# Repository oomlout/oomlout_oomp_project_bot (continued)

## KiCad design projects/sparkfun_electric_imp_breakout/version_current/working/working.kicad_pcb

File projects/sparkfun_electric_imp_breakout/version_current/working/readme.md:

# OOMP Project  
## Electric_Imp_Breakout  by sparkfun  
  
oomp key: oomp_projects_flat_sparkfun_electric_imp_breakout  
(snippet of original readme)  
  
Electric Imp Breakout  
=====================  
  
[  
*Electric Imp Breakout (BOB-12886)*](https://www.sparkfun.com/products/12886)  
  
The Electric Imp Breakout Board allows you to explore the capabilities of the Imp by providing standard 0.1" headers to solder  
as well as the necessary CryptAuthEE IC to identify your prototype to the Imp Cloud service.   
  
Repository Contents  
-------------------  
* **/Hardware** - All Eagle design files (.brd, .sch)  
* **/Production** - Test bed files and production panel files  
  
Product Versions  
----------------  
* [BOB-11400](https://www.sparkfun.com/products/11400)- Version 1.1 for sale on SparkFun.   
  
Version History  
---------------  
* [v1.1](https://github.com/sparkfun/Electric_Imp_Breakout/tree/V_1.1) Version 1.1 of the Imp Breakout, with the old SD socket footprint.  
  
License Information  
-------------------  
The hardware is released under [Creative Commons ShareAlike 4.0 International](https://creativecommons.org/licenses/by-sa/4.0/).  
  
Distributed as-is; no warranty is given.  
  full source readme at [readme_src.md](readme_src.md)  
  
source repo at: [https://github.com/sparkfun/Electric_Imp_Breakout](https://github.com/sparkfun/Electric_Imp_Breakout)  
## Board  

## Schematic  

[schematic pdf](working_schematic.pdf)  
## Images

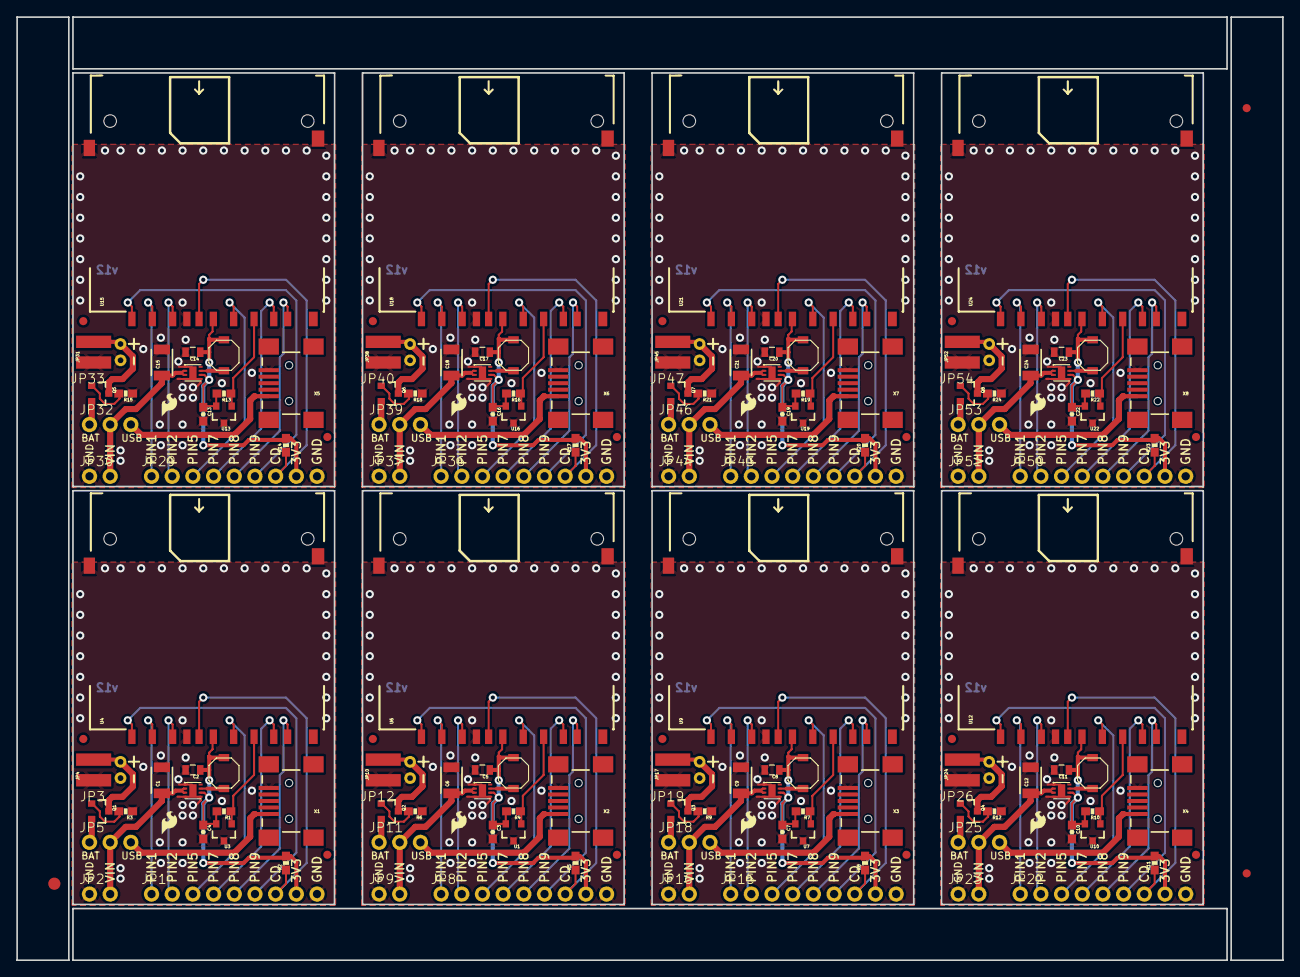
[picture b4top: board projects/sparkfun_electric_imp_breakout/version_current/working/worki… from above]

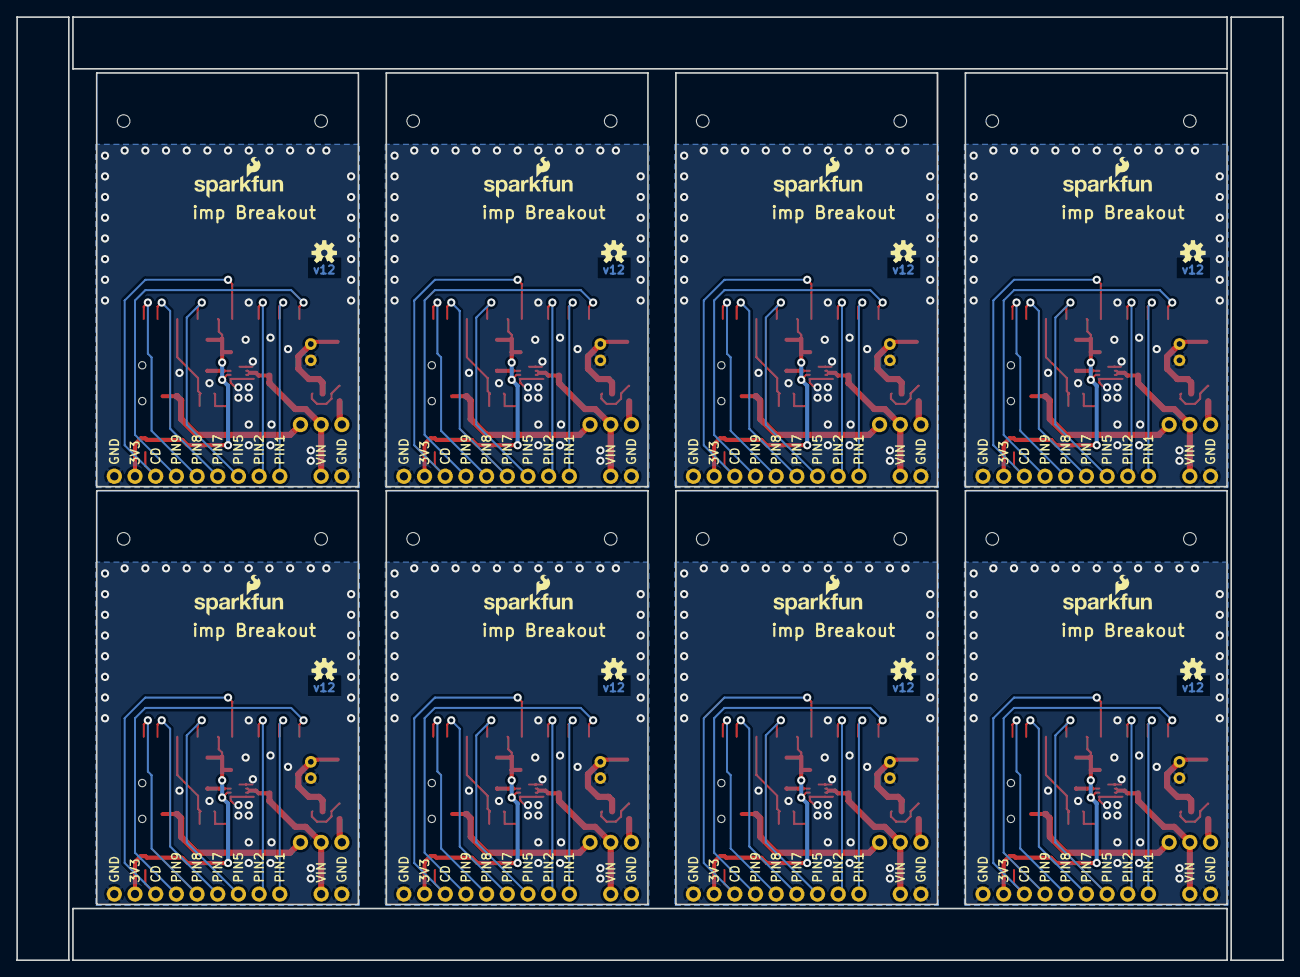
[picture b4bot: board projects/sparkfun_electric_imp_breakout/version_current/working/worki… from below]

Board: 2 copper layers, 155.4 x 115.8 mm, 179 parts (16 on the bottom side), 128 nets.

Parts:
C1, C6, C9, C12, C15, C18, C21, C24: 10uF; 1210
C2, C5, C8, C11, C14, C17, C20, C23: 22uF; 0805
C3, C4, C7, C10, C13, C16, C19, C22: 0.1uF; 0603-CAP
E$1: FIDUCIAL-1.5X3
E$5, E$6: FIDUCIAL-1X2
FID1, FID2, FID3, FID4, FID5, FID6, FID7, FID8, FID9, FID10, FID11, FID12, FID13, FID14, FID15, FID16: FIDUCIAL1X2; FIDUCIAL-1X2
JP1, JP8, JP15, JP22, JP29, JP36, JP43, JP50: M09NO_SILK; 1X09_NO_SILK
JP2, JP9, JP16, JP23, JP30, JP37, JP44, JP51: 1X02_NO_SILK
JP3, JP12, JP19, JP26, JP33, JP40, JP47, JP54: 1X02_SMD
JP4, JP10, JP17, JP24, JP31, JP38, JP45, JP52: JST-2-PTH-NS
JP5, JP11, JP18, JP25, JP32, JP39, JP46, JP53: 1X03_NO_SILK
JP6, JP13, JP20, JP27, JP34, JP41, JP48, JP55: LOGO-SFESK; SFE-LOGO-FLAME
JP7, JP14, JP21, JP28, JP35, JP42, JP49, JP56: SFE_LOGO_NAME_FLAME.1_INCH; SFE_LOGO_NAME_FLAME_.1
L1, L2, L3, L4, L5, L6, L7, L8: 2.2uH; VLF4012A
Q1, Q2, Q3, Q4, Q5, Q6, Q7, Q8: DMG2307L-7; SOT23-3
R1, R3, R4, R6, R7, R9, R10, R12, R13, R15, R16, R18, R19, R21, R22, R24: 100k; 0603-RES
R2, R5, R8, R11, R14, R17, R20, R23: dnp; 0603-RES
U1, U3, U7, U10, U13, U16, U19, U22: ATSHA204-TSU; SOT23-3
U2, U5, U8, U11, U14, U17, U20, U23: TPS62172; WSON-8-PAD
U4, U6, U9, U12, U15, U18, U21, U24: ELECTRIC_IMP; SD_1_1
U$1, U$2, U$3, U$4, U$5, U$6, U$7, U$8: OSHW-LOGOS; OSHW-LOGO-S
X1, X2, X3, X4, X5, X6, X7, X8: USBSMD; USB-MINIB

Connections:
3.3V: C2.1, C4.1, JP1.8, L1.P$2, R1.2, R2.2, U2.6, U3.2, U4.4
3.3V1: C3.1, C5.1, JP8.8, L2.P$2, R4.2, R5.2, U1.2, U5.6, U6.4
3.3V2: C7.1, C8.1, JP15.8, L3.P$2, R7.2, R8.2, U7.2, U8.6, U9.4
3.3V3: C10.1, C11.1, JP22.8, L4.P$2, R10.2, R11.2, U10.2, U11.6, U12.4
3.3V4: C13.1, C14.1, JP29.8, L5.P$2, R13.2, R14.2, U13.2, U14.6, U15.4
3.3V5: C16.1, C17.1, JP36.8, L6.P$2, R16.2, R17.2, U16.2, U17.6, U18.4
3.3V6: C19.1, C20.1, JP43.8, L7.P$2, R19.2, R20.2, U19.2, U20.6, U21.4
3.3V7: C22.1, C23.1, JP50.8, L8.P$2, R22.2, R23.2, U22.2, U23.6, U24.4
CD: JP1.7, R2.1, U4.CD
CD1: JP8.7, R5.1, U6.CD
CD2: JP15.7, R8.1, U9.CD
CD3: JP22.7, R11.1, U12.CD
CD4: JP29.7, R14.1, U15.CD
CD5: JP36.7, R17.1, U18.CD
CD6: JP43.7, R20.1, U21.CD
CD7: JP50.7, R23.1, U24.CD
GND: C1.2, C2.2, C4.2, JP1.9, JP2.1, JP3.1, JP4.1, R3.1, U2.1, U2.4, U2.5, U2.PAD, U3.3, U4.3, U4.SH@1, U4.SH@2, X1.GND
GND1: C3.2, C5.2, C6.2, JP8.9, JP9.1, JP10.1, JP12.1, R6.1, U1.3, U5.1, U5.4, U5.5, U5.PAD, U6.3, U6.SH@1, U6.SH@2, X2.GND
GND2: C7.2, C8.2, C9.2, JP15.9, JP16.1, JP17.1, JP19.1, R9.1, U7.3, U8.1, U8.4, U8.5, U8.PAD, U9.3, U9.SH@1, U9.SH@2, X3.GND
GND3: C10.2, C11.2, C12.2, JP22.9, JP23.1, JP24.1, JP26.1, R12.1, U10.3, U11.1, U11.4, U11.5, U11.PAD, U12.3, U12.SH@1, U12.SH@2, X4.GND
GND4: C13.2, C14.2, C15.2, JP29.9, JP30.1, JP31.1, JP33.1, R15.1, U13.3, U14.1, U14.4, U14.5, U14.PAD, U15.3, U15.SH@1, U15.SH@2, X5.GND
GND5: C16.2, C17.2, C18.2, JP36.9, JP37.1, JP38.1, JP40.1, R18.1, U16.3, U17.1, U17.4, U17.5, U17.PAD, U18.3, U18.SH@1, U18.SH@2, X6.GND
GND6: C19.2, C20.2, C21.2, JP43.9, JP44.1, JP45.1, JP47.1, R21.1, U19.3, U20.1, U20.4, U20.5, U20.PAD, U21.3, U21.SH@1, U21.SH@2, X7.GND
GND7: C22.2, C23.2, C24.2, JP50.9, JP51.1, JP52.1, JP54.1, R24.1, U22.3, U23.1, U23.4, U23.5, U23.PAD, U24.3, U24.SH@1, U24.SH@2, X8.GND
ID: R1.1, U3.1, U4.6
ID1: R4.1, U1.1, U6.6
ID2: R7.1, U7.1, U9.6
ID3: R10.1, U10.1, U12.6
ID4: R13.1, U13.1, U15.6
ID5: R16.1, U16.1, U18.6
ID6: R19.1, U19.1, U21.6
ID7: R22.1, U22.1, U24.6
unnamed: L1.P$1, U2.7
unnamed: Q1.1, R3.2
unnamed: L2.P$1, U5.7
unnamed: JP11.1, Q2.2
unnamed: Q2.1, R6.2
unnamed: JP5.1, Q1.2
unnamed: L3.P$1, U8.7
unnamed: JP18.1, Q3.2
unnamed: Q3.1, R9.2
unnamed: L4.P$1, U11.7
unnamed: JP25.1, Q4.2
unnamed: Q4.1, R12.2
unnamed: L5.P$1, U14.7
unnamed: JP32.1, Q5.2
unnamed: Q5.1, R15.2
unnamed: L6.P$1, U17.7
unnamed: JP39.1, Q6.2
unnamed: Q6.1, R18.2
unnamed: L7.P$1, U20.7
unnamed: JP46.1, Q7.2
unnamed: Q7.1, R21.2
unnamed: L8.P$1, U23.7
unnamed: JP53.1, Q8.2
unnamed: Q8.1, R24.2
PIN1: JP1.1, U4.1
PIN2: JP1.2, U4.2
PIN3: JP8.1, U6.1
PIN4: JP8.2, U6.2
PIN5: JP1.3, U4.5
PIN6: JP8.3, U6.5
PIN7: JP1.4, U4.7
PIN8: JP1.5, U4.8
PIN9: JP1.6, U4.9
PIN10: JP8.4, U6.7
PIN11: JP8.5, U6.8
PIN12: JP8.6, U6.9
PIN13: JP15.1, U9.1
PIN14: JP15.2, U9.2
PIN15: JP15.3, U9.5
PIN16: JP15.4, U9.7
PIN17: JP15.5, U9.8
PIN18: JP15.6, U9.9
PIN19: JP22.1, U12.1
PIN20: JP22.2, U12.2
PIN21: JP22.3, U12.5
PIN22: JP22.4, U12.7
PIN23: JP22.5, U12.8
PIN24: JP22.6, U12.9
PIN25: JP29.1, U15.1
PIN26: JP29.2, U15.2
PIN27: JP29.3, U15.5
PIN28: JP29.4, U15.7
PIN29: JP29.5, U15.8
PIN30: JP29.6, U15.9
PIN31: JP36.1, U18.1
PIN32: JP36.2, U18.2
PIN33: JP36.3, U18.5
PIN34: JP36.4, U18.7
PIN35: JP36.5, U18.8
PIN36: JP36.6, U18.9
PIN37: JP43.1, U21.1
PIN38: JP43.2, U21.2
PIN39: JP43.3, U21.5
PIN40: JP43.4, U21.7
PIN41: JP43.5, U21.8
PIN42: JP43.6, U21.9
PIN43: JP50.1, U24.1
PIN44: JP50.2, U24.2
PIN45: JP50.3, U24.5
PIN46: JP50.4, U24.7
PIN47: JP50.5, U24.8
PIN48: JP50.6, U24.9
VBAT: JP3.2, JP4.2, Q1.3
VBAT1: JP10.2, JP12.2, Q2.3
VBAT2: JP17.2, JP19.2, Q3.3
VBAT3: JP24.2, JP26.2, Q4.3
VBAT4: JP31.2, JP33.2, Q5.3
VBAT5: JP38.2, JP40.2, Q6.3
VBAT6: JP45.2, JP47.2, Q7.3
VBAT7: JP52.2, JP54.2, Q8.3
VIN: C1.1, JP2.2, JP5.2, U2.2, U2.3
VIN1: C6.1, JP9.2, JP11.2, U5.2, U5.3
VIN2: C9.1, JP16.2, JP18.2, U8.2, U8.3
VIN3: C12.1, JP23.2, JP25.2, U11.2, U11.3
VIN4: C15.1, JP30.2, JP32.2, U14.2, U14.3
VIN5: C18.1, JP37.2, JP39.2, U17.2, U17.3
VIN6: C21.1, JP44.2, JP46.2, U20.2, U20.3
VIN7: C24.1, JP51.2, JP53.2, U23.2, U23.3
VUSB: JP5.3, X1.VBUS
VUSB1: JP11.3, X2.VBUS
VUSB2: JP18.3, X3.VBUS
VUSB3: JP25.3, X4.VBUS
VUSB4: JP32.3, X5.VBUS
VUSB5: JP39.3, X6.VBUS
VUSB6: JP46.3, X7.VBUS
VUSB7: JP53.3, X8.VBUS

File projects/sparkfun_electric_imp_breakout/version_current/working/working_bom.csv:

Row,Description,Part,References,Value,Footprint,Quantity Per PCB,Status,Datasheet
1,,0.1UF-25V(+80/-20%)(0603),C4,0.1uF,0603-CAP,1, ,
2,,10UF50V20%(1210),C1,10uF,1210,1, ,
3,,22UF-6.3V-20%(0805),C2,22uF,0805,1, ,
4,,FRAME-LETTER,FRAME1,FRAME-LETTER,CREATIVE_COMMONS,1, ,
5,,LOGO-SFESK,JP6,LOGO-SFESK,SFE-LOGO-FLAME,1, ,
6,,M02-JST-2-PTH-NO_SILK,JP4,M02-JST-2-PTH-NO_SILK,JST-2-PTH-NS,1, ,
7,,M021X02_NO_SILK,JP2,M021X02_NO_SILK,1X02_NO_SILK,1, ,
8,,M02SMD,JP3,M02SMD,1X02_SMD,1, ,
9,,M031X03_NO_SILK,JP5,M031X03_NO_SILK,1X03_NO_SILK,1, ,
10,,M09NO_SILK,JP1,M09NO_SILK,1X09_NO_SILK,1, ,
11,,SFE_LOGO_NAME_FLAME.1_INCH,JP7,SFE_LOGO_NAME_FLAME.1_INCH,SFE_LOGO_NAME_FLAME_.1,1, ,
12,,INDUCTORVLF4012A,L1,2.2uH,VLF4012A,1, ,
13,,MOSFET-PCHANNELSMD,Q1,MOSFET-PCHANNELSMD,SOT23-3,1, ,
14,,100KOHM1/10W1%(0603),R1 R3,100k,0603-RES,2, ,
15,,ATSHA204-TSU,U3,ATSHA204-TSU,SOT23-3,1, ,
16,,ELECTRIC_IMP,U4,ELECTRIC_IMP,SD_1_1,1, ,
17,,TPS62172,U2,TPS62172,WSON-8-PAD,1, ,
18,,OSHW-LOGOS,U$5,OSHW-LOGOS,OSHW-LOGO-S,1, ,
19,,REVISION,U$3,REVISION,REVISION,1, ,
20,,USBSMD,X1,USBSMD,USB-MINIB,1, ,





Project info:
Schematic:,working
Variant:,default
Revision:,
Date:,2023-08-06_12-56-01
KiCad Version:,7.0.6-7.0.6~ubuntu22.04.1
Statistics:
Component Groups:,21
Component Count:,22 (0 SMD/ 0 THT)
Fitted Components:,21 (0 SMD/ 0 THT)
Number of PCBs:,1
Total Components:,21

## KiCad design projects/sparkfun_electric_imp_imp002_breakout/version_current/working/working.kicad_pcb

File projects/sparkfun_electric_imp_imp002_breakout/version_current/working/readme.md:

# OOMP Project  
## Electric_Imp_imp002_Breakout  by sparkfun  
  
oomp key: oomp_projects_flat_sparkfun_electric_imp_imp002_breakout  
(snippet of original readme)  
  
SparkFun Electric Imp imp002 Breakout  
============================  

[*Electric Imp imp002 Breakout (BOB-12958)*](https://www.sparkfun.com/products/12958)  
  
The imp002 is a surface mount Electric Imp module with its own breakout board and more pins than the original imp001 card.  

Repository Contents  
-------------------  
* **/Documentation** - SVG files of the board layout.  
* **/Hardware** - Eagle PCB layout files  
* **/Production** - Files to support SparkFun production  
  
Documentation  
--------------  
  
* **[Hookup Guide](https://learn.sparkfun.com/tutorials/electric-imp-breakout-hookup-guide)** - Basic hookup guide  
  
Product Versions  
----------------  
  
* [BOB-12958](https://www.sparkfun.com/products/12958)- Hardware version 1.0.   
  
Version History  
---------------  
  
License Information  
-------------------  
  
This product is _**open source**_!   
  
Please review the LICENSE.md file for license information.   
  
If you have any questions or concerns on licensing, please contact techsupport@sparkfun.com.  
  
Distributed as-is; no warranty is given.  
  
- Your friends at SparkFun.  
  
  full source readme at [readme_src.md](readme_src.md)  
  
source repo at: [https://github.com/sparkfun/Electric_Imp_imp002_Breakout](https://github.com/sparkfun/Electric_Imp_imp002_Breakout)  
## Board  

## Schematic  

[schematic pdf](working_schematic.pdf)  
## Images

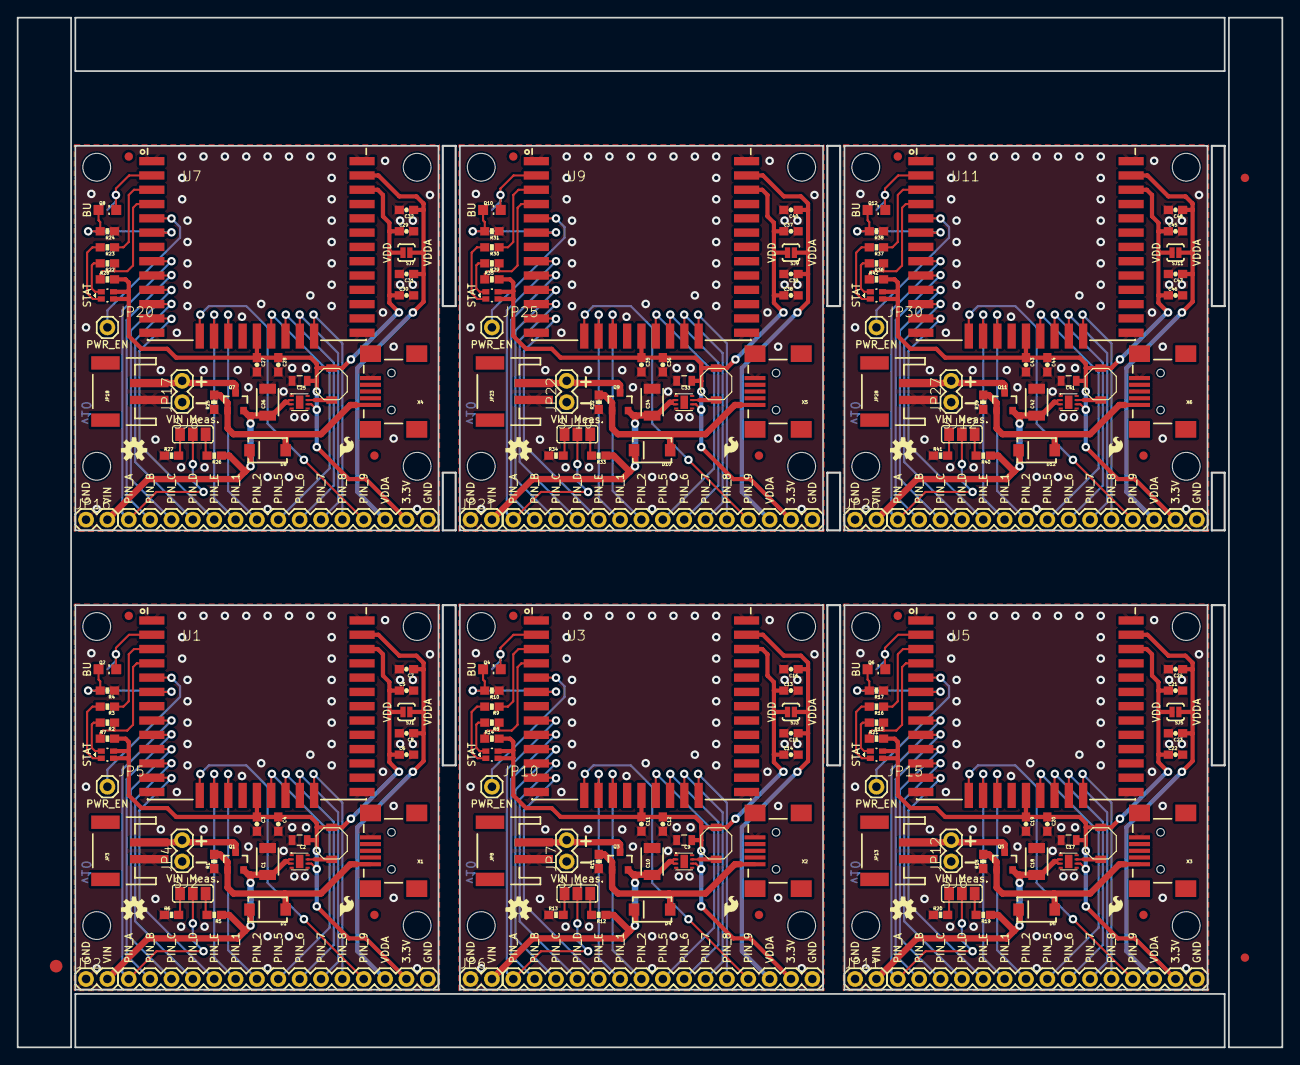
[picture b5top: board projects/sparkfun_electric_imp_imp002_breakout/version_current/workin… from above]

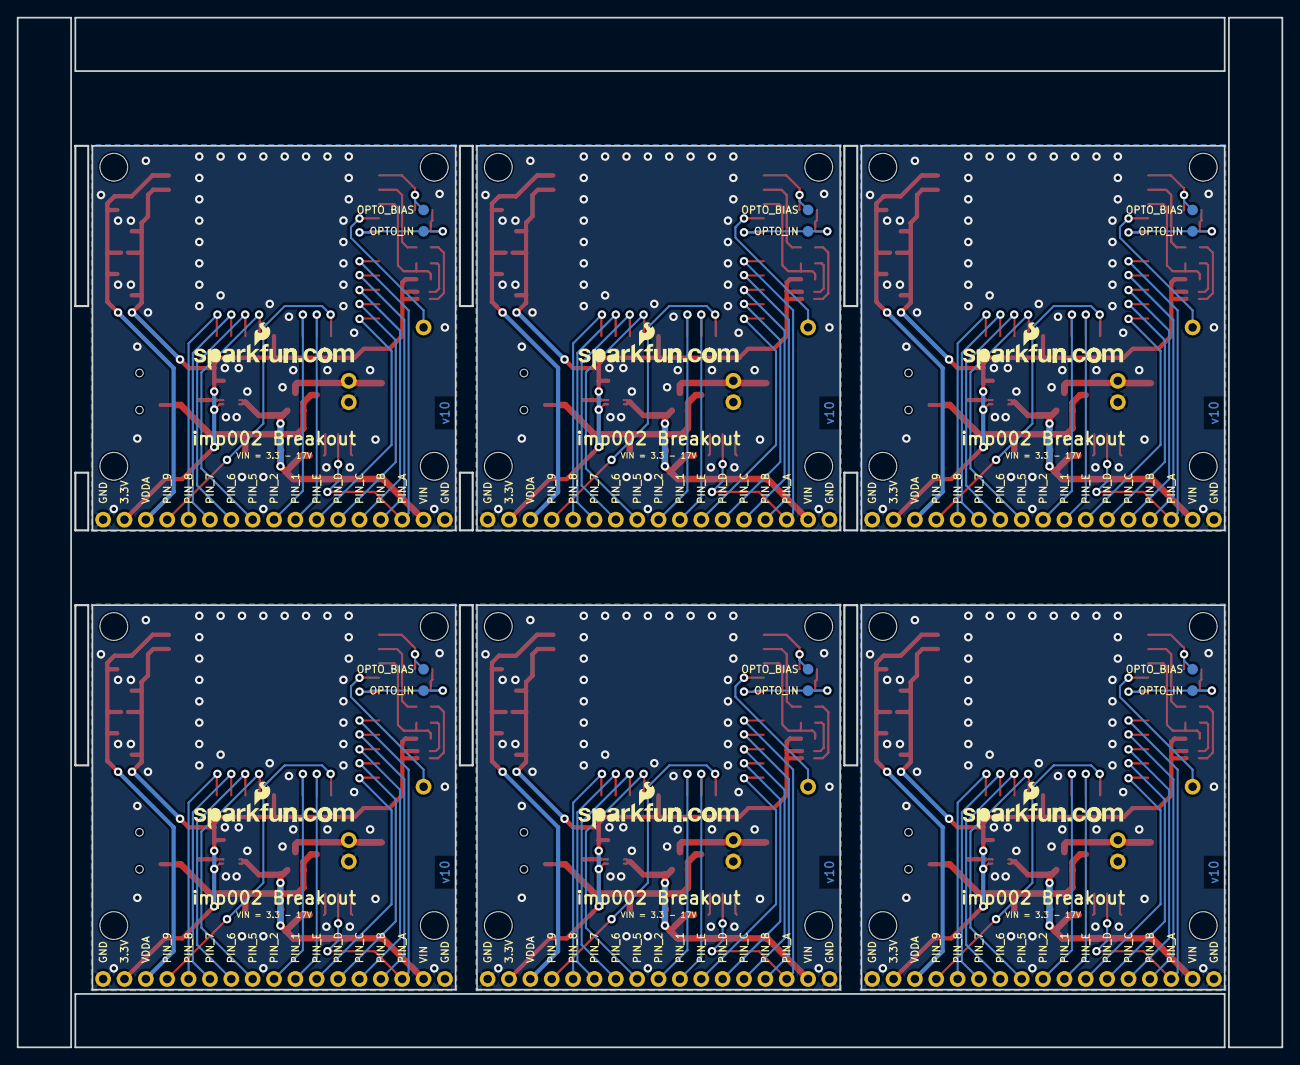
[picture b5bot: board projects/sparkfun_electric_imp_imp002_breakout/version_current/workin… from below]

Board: 4 copper layers, 150.4 x 122.4 mm, 249 parts (18 on the bottom side), 168 nets.

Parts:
C1, C10, C18, C26, C34, C42: 10uF; 1210
C2, C9, C17, C25, C33, C41: 22uF; 0805
C3, C5, C7, C11, C13, C16, C19, C21, C24, C27, C29, C32, C35, C37, C40, C43, C45, C48: 100pF; 0603-CAP
C4, C6, C12, C14, C20, C22, C28, C30, C36, C38, C44, C46: 1.0uF; 0603-CAP
C8, C15, C23, C31, C39, C47: DNP; 0603-CAP
D1, D4, D6, D8, D10, D12: MBRA140; SMA-DIODE
D2, D3, D5, D7, D9, D11: LED-RGLTST-C195KGJRKT; LTST-C195KGJRKT
E$1: FIDUCIAL-1.5X3
E$3, E$5: FIDUCIAL-1X2
FID1, FID2, FID3, FID4, FID5, FID6, FID7, FID8, FID9, FID10, FID11, FID12: FIDUCIAL1X2; FIDUCIAL-1X2
JP1, JP9, JP14, JP19, JP24, JP29: M15; 1X15
JP2, JP4, JP6, JP7, JP11, JP12, JP16, JP17, JP21, JP22, JP26, JP27: M02PTH; 1X02
JP3, JP8, JP13, JP18, JP23, JP28: M02-JST-2MM-SMT; JST-2-SMD
JP5, JP10, JP15, JP20, JP25, JP30: M01PTH; 1X01
L1, L2, L3, L4, L5, L6: 2.2uH; VLF4012A
LOGO1, LOGO3, LOGO5, LOGO7, LOGO9, LOGO11: OSHW-LOGOS; OSHW-LOGO-S
LOGO2, LOGO4, LOGO6, LOGO8, LOGO10, LOGO12: SFE_LOGO_FLAME.1_INCH; SFE_LOGO_FLAME_.1
Q1, Q3, Q5, Q7, Q9, Q11: DMG2307L; SOT23-3
Q2, Q4, Q6, Q8, Q10, Q12: PT17-21C-L41-TR8
R1, R11, R18, R25, R32, R39: 100k; 0603-RES
R2, R3, R8, R9, R15, R16, R22, R23, R29, R30, R36, R37: 330; 0603-RES
R4, R5, R10, R12, R17, R19, R24, R26, R31, R33, R38, R40: 33k; 0603-RES
R6, R13, R20, R27, R34, R41: 62k; 0603-RES
R7, R14, R21, R28, R35, R42: 10K; 0603-RES
SJ1, SJ3, SJ5, SJ7, SJ9, SJ11: JUMPER-PAD-2-NC_BY_PASTE; PAD-JUMPER-2-NC_BY_PASTE_YES_SILK
SJ2, SJ4, SJ6, SJ8, SJ10, SJ12: JUMPER-PAD-3-NOFULL_BOX_SILK; PAD-JUMPER-3-NO_YES_SILK_FULL_BOX
STANDOFF1, STANDOFF2, STANDOFF3, STANDOFF4, STANDOFF5, STANDOFF6, STANDOFF7, STANDOFF8, STANDOFF9, STANDOFF10, STANDOFF11, STANDOFF12, STANDOFF13, STANDOFF14, STANDOFF15, STANDOFF16, STANDOFF17, STANDOFF18, STANDOFF19, STANDOFF20, STANDOFF21, STANDOFF22, STANDOFF23, STANDOFF24: STAND-OFF
TP1, TP2, TP3, TP4, TP5, TP6, TP7, TP8, TP9, TP10, TP11, TP12: TEST-POINT3X5; PAD.03X.05
U1, U3, U5, U7, U9, U11: imp002; ELECTRIC_IMP_IMP002
U2, U4, U6, U8, U10, U12: TPS62172; WSON-8-PAD
U$1, U$2, U$3, U$4, U$5, U$9: SFE_LOGO_NAME_WEB; SFE-NEW-WEBLOGO
X1, X2, X3, X4, X5, X6: USBSMD; USB-MINIB

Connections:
3.3V: C2.1, C3.1, C4.1, C5.1, C6.1, D2.P$1, D2.P$2, JP1.2, L1.P$2, R7.2, SJ1.2, U1.18, U1.33, U2.6
3.3V1: C9.1, C11.1, C12.1, C13.1, C14.1, D3.P$1, D3.P$2, JP9.2, L2.P$2, R14.2, SJ3.2, U3.18, U3.33, U4.6
3.3V2: C17.1, C19.1, C20.1, C21.1, C22.1, D5.P$1, D5.P$2, JP14.2, L3.P$2, R21.2, SJ5.2, U5.18, U5.33, U6.6
3.3V3: C25.1, C27.1, C28.1, C29.1, C30.1, D7.P$1, D7.P$2, JP19.2, L4.P$2, R28.2, SJ7.2, U7.18, U7.33, U8.6
3.3V4: C33.1, C35.1, C36.1, C37.1, C38.1, D9.P$1, D9.P$2, JP24.2, L5.P$2, R35.2, SJ9.2, U9.18, U9.33, U10.6
3.3V5: C41.1, C43.1, C44.1, C45.1, C46.1, D11.P$1, D11.P$2, JP29.2, L6.P$2, R42.2, SJ11.2, U11.18, U11.33, U12.6
GND: C1.2, C2.2, C3.2, C4.2, C5.2, C6.2, C7.2, C8.2, JP1.1, JP2.1, JP3.1, JP4.1, R1.1, R4.1, R6.1, U1.1, U1.7, U1.13, U1.17, U1.23, U1.24, U1.25, U1.26, U1.27, U1.28, U1.29, U1.30, U1.31, U1.32, U1.35, U2.1, U2.4, U2.5, U2.PAD, X1.GND
GND1: C9.2, C10.2, C11.2, C12.2, C13.2, C14.2, C15.2, C16.2, JP6.1, JP7.1, JP8.1, JP9.1, R10.1, R11.1, R13.1, U3.1, U3.7, U3.13, U3.17, U3.23, U3.24, U3.25, U3.26, U3.27, U3.28, U3.29, U3.30, U3.31, U3.32, U3.35, U4.1, U4.4, U4.5, U4.PAD, X2.GND
GND2: C17.2, C18.2, C19.2, C20.2, C21.2, C22.2, C23.2, C24.2, JP11.1, JP12.1, JP13.1, JP14.1, R17.1, R18.1, R20.1, U5.1, U5.7, U5.13, U5.17, U5.23, U5.24, U5.25, U5.26, U5.27, U5.28, U5.29, U5.30, U5.31, U5.32, U5.35, U6.1, U6.4, U6.5, U6.PAD, X3.GND
GND3: C25.2, C26.2, C27.2, C28.2, C29.2, C30.2, C31.2, C32.2, JP16.1, JP17.1, JP18.1, JP19.1, R24.1, R25.1, R27.1, U7.1, U7.7, U7.13, U7.17, U7.23, U7.24, U7.25, U7.26, U7.27, U7.28, U7.29, U7.30, U7.31, U7.32, U7.35, U8.1, U8.4, U8.5, U8.PAD, X4.GND
GND4: C33.2, C34.2, C35.2, C36.2, C37.2, C38.2, C39.2, C40.2, JP21.1, JP22.1, JP23.1, JP24.1, R31.1, R32.1, R34.1, U9.1, U9.7, U9.13, U9.17, U9.23, U9.24, U9.25, U9.26, U9.27, U9.28, U9.29, U9.30, U9.31, U9.32, U9.35, U10.1, U10.4, U10.5, U10.PAD, X5.GND
GND5: C41.2, C42.2, C43.2, C44.2, C45.2, C46.2, C47.2, C48.2, JP26.1, JP27.1, JP28.1, JP29.1, R38.1, R39.1, R41.1, U11.1, U11.7, U11.13, U11.17, U11.23, U11.24, U11.25, U11.26, U11.27, U11.28, U11.29, U11.30, U11.31, U11.32, U11.35, U12.1, U12.4, U12.5, U12.PAD, X6.GND
LED_G: R3.1, U1.3
LED_G1: R9.1, U3.3
LED_G2: R16.1, U5.3
LED_G3: R23.1, U7.3
LED_G4: R30.1, U9.3
LED_G5: R37.1, U11.3
LED_R: R2.1, R7.1, U1.4
LED_R1: R8.1, R14.1, U3.4
LED_R2: R15.1, R21.1, U5.4
LED_R3: R22.1, R28.1, U7.4
LED_R4: R29.1, R35.1, U9.4
LED_R5: R36.1, R42.1, U11.4
unnamed: L1.P$1, U2.7
unnamed: D1.A, Q1.1, R1.2, X1.VBUS
unnamed: L2.P$1, U4.7
unnamed: D2.P$4, R2.2
unnamed: D2.P$3, R3.2
unnamed: R5.2, SJ2.3
unnamed: R6.2, SJ2.1
unnamed: D3.P$4, R8.2
unnamed: D3.P$3, R9.2
unnamed: D4.A, Q3.1, R11.2, X2.VBUS
unnamed: R12.2, SJ4.3
unnamed: R13.2, SJ4.1
unnamed: L3.P$1, U6.7
unnamed: D5.P$4, R15.2
unnamed: D5.P$3, R16.2
unnamed: D6.A, Q5.1, R18.2, X3.VBUS
unnamed: R19.2, SJ6.3
unnamed: R20.2, SJ6.1
unnamed: L4.P$1, U8.7
unnamed: D7.P$4, R22.2
unnamed: D7.P$3, R23.2
unnamed: D8.A, Q7.1, R25.2, X4.VBUS
unnamed: R26.2, SJ8.3
unnamed: R27.2, SJ8.1
unnamed: L5.P$1, U10.7
unnamed: D9.P$4, R29.2
unnamed: D9.P$3, R30.2
unnamed: D10.A, Q9.1, R32.2, X5.VBUS
unnamed: R33.2, SJ10.3
unnamed: R34.2, SJ10.1
unnamed: L6.P$1, U12.7
unnamed: D11.P$4, R36.2
unnamed: D11.P$3, R37.2
unnamed: D12.A, Q11.1, R39.2, X6.VBUS
unnamed: R40.2, SJ12.3
unnamed: R41.2, SJ12.1
OPTO_BIAS: Q2.C, TP1.P$1, U1.2
OPTO_BIAS1: Q4.C, TP3.P$1, U3.2
OPTO_BIAS2: Q6.C, TP5.P$1, U5.2
OPTO_BIAS3: Q8.C, TP7.P$1, U7.2
OPTO_BIAS4: Q10.C, TP9.P$1, U9.2
OPTO_BIAS5: Q12.C, TP11.P$1, U11.2
OPTO_IN: Q2.E, R4.2, TP2.P$1, U1.6
OPTO_IN1: Q4.E, R10.2, TP4.P$1, U3.6
OPTO_IN2: Q6.E, R17.2, TP6.P$1, U5.6
OPTO_IN3: Q8.E, R24.2, TP8.P$1, U7.6
OPTO_IN4: Q10.E, R31.2, TP10.P$1, U9.6
OPTO_IN5: Q12.E, R38.2, TP12.P$1, U11.6
PIN_1: JP1.10, U1.15
PIN_2: JP1.9, U1.16
PIN_3: JP9.10, U3.15
PIN_4: JP9.9, U3.16
PIN_5: JP1.8, U1.19
PIN_6: JP1.7, U1.20
PIN_7: JP1.6, U1.21
PIN_8: JP1.5, U1.22
PIN_9: JP1.4, U1.14
PIN_10: JP9.8, U3.19
PIN_11: JP9.7, U3.20
PIN_12: JP9.6, U3.21
PIN_13: JP9.5, U3.22
PIN_14: JP9.4, U3.14
PIN_15: JP14.10, U5.15
PIN_16: JP14.9, U5.16
PIN_17: JP14.8, U5.19
PIN_18: JP14.7, U5.20
PIN_19: JP14.6, U5.21
PIN_20: JP14.5, U5.22
PIN_21: JP14.4, U5.14
PIN_22: JP19.10, U7.15
PIN_23: JP19.9, U7.16
PIN_24: JP19.8, U7.19
PIN_25: JP19.7, U7.20
PIN_26: JP19.6, U7.21
PIN_27: JP19.5, U7.22
PIN_28: JP19.4, U7.14
PIN_29: JP24.10, U9.15
PIN_30: JP24.9, U9.16
PIN_31: JP24.8, U9.19
PIN_32: JP24.7, U9.20
PIN_33: JP24.6, U9.21
PIN_34: JP24.5, U9.22
PIN_35: JP24.4, U9.14
PIN_36: JP29.10, U11.15
PIN_37: JP29.9, U11.16
PIN_38: JP29.8, U11.19
PIN_39: JP29.7, U11.20
PIN_40: JP29.6, U11.21
PIN_41: JP29.5, U11.22
PIN_42: JP29.4, U11.14
PIN_A: JP1.15, SJ2.2, U1.8
PIN_A1: JP9.15, SJ4.2, U3.8
PIN_A2: JP14.15, SJ6.2, U5.8
PIN_A3: JP19.15, SJ8.2, U7.8
PIN_A4: JP24.15, SJ10.2, U9.8
PIN_A5: JP29.15, SJ12.2, U11.8
PIN_B: JP1.14, U1.9
PIN_B1: JP9.14, U3.9
PIN_B2: JP14.14, U5.9
PIN_B3: JP19.14, U7.9
PIN_B4: JP24.14, U9.9
PIN_B5: JP29.14, U11.9
PIN_C: JP1.13, U1.10
PIN_C1: JP9.13, U3.10
PIN_C2: JP14.13, U5.10
PIN_C3: JP19.13, U7.10
PIN_C4: JP24.13, U9.10
PIN_C5: JP29.13, U11.10
PIN_D: JP1.12, U1.11
PIN_D1: JP9.12, U3.11
PIN_D2: JP14.12, U5.11
PIN_D3: JP19.12, U7.11
PIN_D4: JP24.12, U9.11
PIN_D5: JP29.12, U11.11
PIN_E: JP1.11, U1.12
PIN_E1: JP9.11, U3.12
PIN_E2: JP14.11, U5.12
PIN_E3: JP19.11, U7.12
PIN_E4: JP24.11, U9.12
PIN_E5: JP29.11, U11.12
POWER_EN: JP5.1, U1.5
POWER_EN1: JP10.1, U3.5
POWER_EN2: JP15.1, U5.5
POWER_EN3: JP20.1, U7.5
POWER_EN4: JP25.1, U9.5
POWER_EN5: JP30.1, U11.5
VBAT: JP3.2, JP4.2, Q1.3
VBAT1: JP7.2, JP8.2, Q3.3
VBAT2: JP12.2, JP13.2, Q5.3
VBAT3: JP17.2, JP18.2, Q7.3
VBAT4: JP22.2, JP23.2, Q9.3
VBAT5: JP27.2, JP28.2, Q11.3
VDDA: C7.1, C8.1, JP1.3, SJ1.1, U1.34
VDDA1: C15.1, C16.1, JP9.3, SJ3.1, U3.34
VDDA2: C23.1, C24.1, JP14.3, SJ5.1, U5.34
VDDA3: C31.1, C32.1, JP19.3, SJ7.1, U7.34
VDDA4: C39.1, C40.1, JP24.3, SJ9.1, U9.34
VDDA5: C47.1, C48.1, JP29.3, SJ11.1, U11.34
VIN: C1.1, D1.C, JP2.2, Q1.2, R5.1, U2.2, U2.3
VIN1: C10.1, D4.C, JP6.2, Q3.2, R12.1, U4.2, U4.3
VIN2: C18.1, D6.C, JP11.2, Q5.2, R19.1, U6.2, U6.3
VIN3: C26.1, D8.C, JP16.2, Q7.2, R26.1, U8.2, U8.3
VIN4: C34.1, D10.C, JP21.2, Q9.2, R33.1, U10.2, U10.3
VIN5: C42.1, D12.C, JP26.2, Q11.2, R40.1, U12.2, U12.3

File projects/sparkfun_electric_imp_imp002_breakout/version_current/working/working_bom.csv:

Row,Description,Part,References,Value,Footprint,Quantity Per PCB,Status,Datasheet,PROD_ID
1,,SparkFun-Capacitors_CAP0603-CAP,C3 C5 C7,100pF,0603-CAP,3, ,,CAP-07883
2,,1.0UF-16V-10%(0603),C4 C6,1.0uF,0603-CAP,2, ,,
3,,CAP1210,C1,10uF,1210,1, ,,
4,,CAP0805,C2,22uF,0805,1, ,,CAP-08402
5,,DIODE-SCHOTTKY-MBRA140,D1,DIODE-SCHOTTKY-MBRA140,SMA-DIODE,1, ,,
6,,LED-RGLTST-C195KGJRKT,D2,LED-RGLTST-C195KGJRKT,LTST-C195KGJRKT,1, ,,
7,,FRAME-LETTER,FRAME1,FRAME-LETTER,CREATIVE_COMMONS,1, ,,
8,,M01PTH,JP5,M01PTH,1X01,1, ,,
9,,M02-JST-2MM-SMT,JP3,M02-JST-2MM-SMT,JST-2-SMD,1, ,,
10,,M02PTH,JP2 JP4,M02PTH,1X02,2, ,,
11,,M15,JP1,M15,1X15,1, ,,
12,,INDUCTORVLF4012A,L1,2.2uH,VLF4012A,1, ,,
13,,OSHW-LOGOS,LOGO1,OSHW-LOGOS,OSHW-LOGO-S,1, ,,
14,,SFE_LOGO_FLAME.1_INCH,LOGO2,SFE_LOGO_FLAME.1_INCH,SFE_LOGO_FLAME_.1,1, ,,
15,,MOSFET-PCHANNELDMG2307L,Q1,MOSFET-PCHANNELDMG2307L,SOT23-3,1, ,,
16,,PHOTOTRANSISTORPT17-21C-L41-TR8,Q2,PT17-21C-L41-TR8,PT17-21C-L41-TR8,1, ,,
17,,330OHM1/10W1%(0603),R2 R3,330,0603-RES,2, ,,
18,,10KOHM1/10W1%(0603)0603,R7,10K,0603-RES,1, ,,
19,,33KOHM1/10W1%(0603),R4 R5,33k,0603-RES,2, ,,
20,,RESISTOR0603,R6,62k,0603-RES,1, ,,RES-09993
21,,100KOHM1/10W1%(0603),R1,100k,0603-RES,1, ,,
22,,JUMPER-PAD-2-NC_BY_PASTE,SJ1,JUMPER-PAD-2-NC_BY_PASTE,PAD-JUMPER-2-NC_BY_PASTE_YES_SILK,1, ,,
23,,JUMPER-PAD-3-NOFULL_BOX_SILK,SJ2,JUMPER-PAD-3-NOFULL_BOX_SILK,PAD-JUMPER-3-NO_YES_SILK_FULL_BOX,1, ,,
24,,STAND-OFF,STANDOFF1 STANDOFF2 STANDOFF3 STANDOFF4,STAND-OFF,STAND-OFF,4, ,,
25,,ELECTRIC_IMP_IMP002,U1,ELECTRIC_IMP_IMP002,ELECTRIC_IMP_IMP002,1, ,,
26,,TPS62172,U2,TPS62172,WSON-8-PAD,1, ,,
27,,SFE_LOGO_NAME_WEB,U$9,SFE_LOGO_NAME_WEB,SFE-NEW-WEBLOGO,1, ,,
28,,USBSMD,X1,USBSMD,USB-MINIB,1, ,,





Project info:
Schematic:,working
Variant:,default
Revision:,
Date:,2023-08-06_12-56-01
KiCad Version:,7.0.6-7.0.6~ubuntu22.04.1
Statistics:
Component Groups:,29
Component Count:,38 (0 SMD/ 0 THT)
Fitted Components:,37 (0 SMD/ 0 THT)
Number of PCBs:,1
Total Components:,37

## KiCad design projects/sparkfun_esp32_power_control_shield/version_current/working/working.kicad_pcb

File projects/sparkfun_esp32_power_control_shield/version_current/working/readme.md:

# OOMP Project  
## ESP32_Power_Control_Shield  by sparkfun  
  
oomp key: oomp_projects_flat_sparkfun_esp32_power_control_shield  
(snippet of original readme)  
  
ESP32 Thing Power Control Shield  
=======  

*[SparkFun ESP32 Thing Power Control Shield](https://www.sparkfun.com/products/14155)*  
  
The ESP32 Thing Power Control Shield is a small adapter board for the [ESP32 Thing](https://www.sparkfun.com/products/13907). The shield gives the ESP32 Thing the power to switch loads of up to 5A between 5 and 28VDC. The shield has 6 output pins to connect loads to, and three current sensors connected to outputs 2, 4, and 6. Operational amplifiers are by default configured as voltage followers, but feedback resistors are broken out to increase the gain of the non-inverting op-amp, which allows for greater precision depending on the maximum expected loads.   
  
Repository Contents  
-------------------  
  
* **/Production** - Panelized version of the design for production  
* **/Hardware** - All Eagle design files (.brd, .sch)  
  
License Information  
-------------------  
  
This design is [OSHW](http://www.oshwa.org/definition/) and public domain but you buy me a beer if you use this and we meet someday ([Beerware license](http://en.wikipedia.org/wiki/Beerware)).  
  full source readme at [readme_src.md](readme_src.md)  
  
source repo at: [https://github.com/sparkfun/ESP32_Power_Control_Shield](https://github.com/sparkfun/ESP32_Power_Control_Shield)  
## Board  

## Schematic  

[schematic pdf](working_schematic.pdf)  
## Images

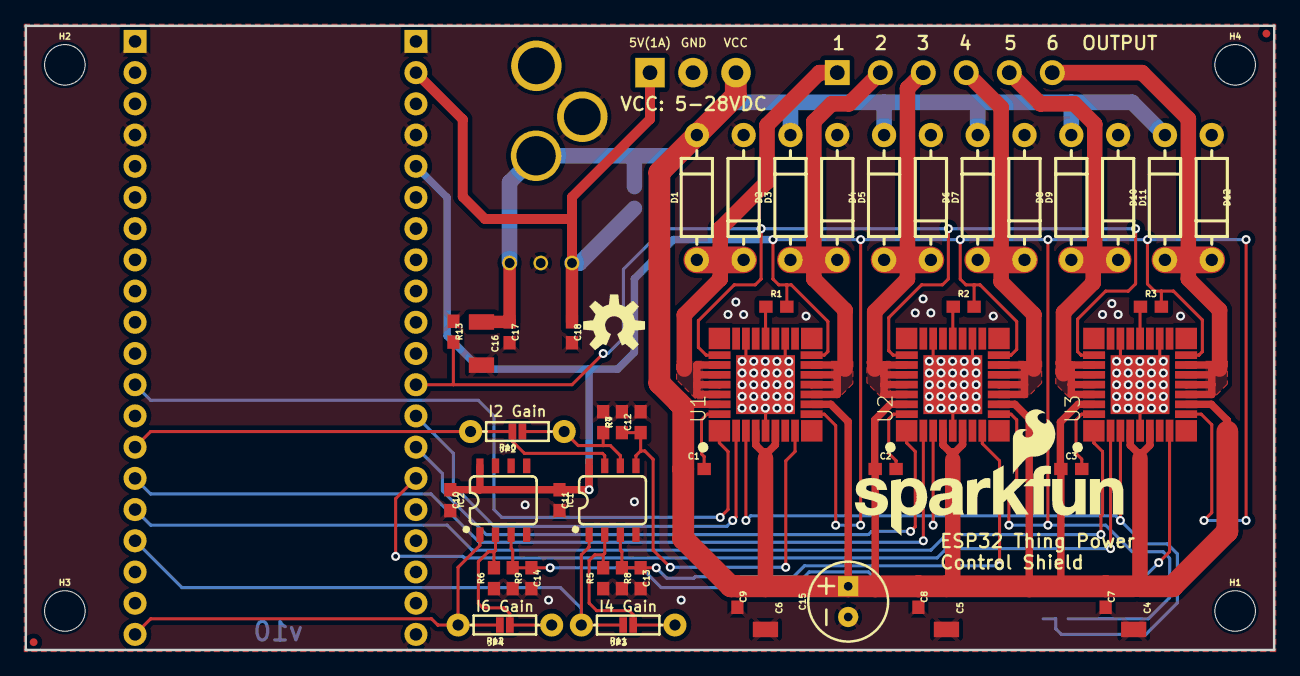
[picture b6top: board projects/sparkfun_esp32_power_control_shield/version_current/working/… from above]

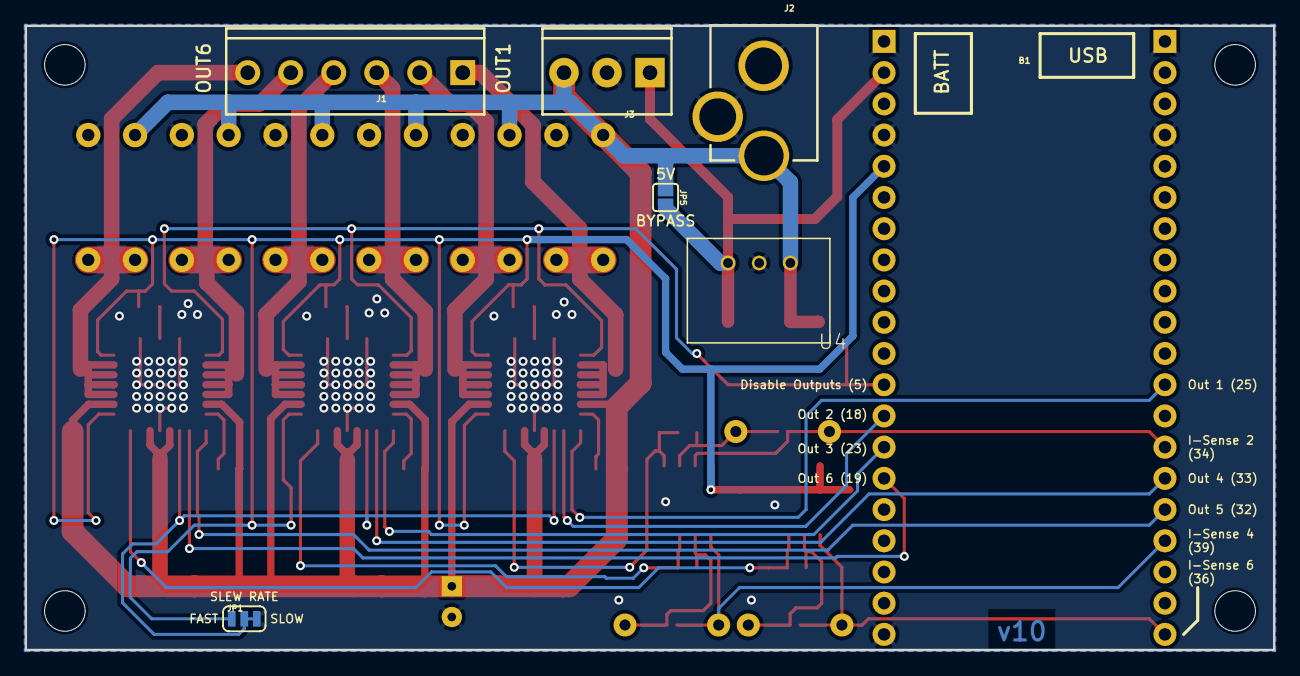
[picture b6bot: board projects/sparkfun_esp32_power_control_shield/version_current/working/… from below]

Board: 2 copper layers, 101.6 x 50.8 mm, 68 parts (7 on the bottom side), 33 nets.

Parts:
B1: ESP32_THING
C1, C2, C3: 33nF; 0603
C4, C5, C6, C16: 10uF; 1210
C7, C8, C9, C10, C11, C17, C18: 0.1uF; 0603
C12, C13, C14: 1.0uF; 0603
C15: Ext.; CPOL-RADIAL-2.5MM-6.5MM
D1, D2, D3, D4, D5, D6, D7, D8, D9, D10, D11, D12: 1N4001; DIODE-1N4001
FD1, FD2: FIDUCIALUFIDUCIAL; FIDUCIAL-MICRO
FRAME1: FRAME-LETTER; CREATIVE_COMMONS
H1, H2, H3, H4: STAND-OFF
IC1, IC2: LMV358; SO08
J1: SCREWTERMINAL-3.5MM-6
J2: POWER_JACKPTH_LOCK; POWER_JACK_PTH_LOCK
J3: SCREWTERMINAL-3.5MM-3
JP1: SMT-JUMPER_3_1-NC_TRACE_SILK
JP2, JP3, JP4: SMT-JUMPER_2_NC_PASTE_NO-SILK
JP5: 5V Bypass; SMT-JUMPER_2_NO_SILK
LOGO1: SFE_LOGO_NAME_FLAME.2_INCH; SFE_LOGO_NAME_FLAME_.2
LOGO2: OSHW-LOGOM; OSHW-LOGO-M
R1, R2, R3, R4, R5, R6: 10k; 0603
R7, R8, R9: 220; 0603
R10, R11, R12: AXIAL-0.3
R13: 1k; 0603
U1, U2, U3: MC33926; 32-PQFN
U4: R-78E5.0-1.0; DC-DC_CONVERTER_78XX
U$1: ORDERING_INSTRUCTIONS

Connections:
3.3V: B1.36, C10.1, C11.1, IC1.8, IC2.8, JP1.1, R1.2, R2.2, R3.2, U1.P$10, U1.P$16, U2.P$10, U2.P$16, U3.P$10, U3.P$16
5V: B1.39, C18.1, J3.1, JP5.2, U4.VOUT
CTRL_1: B1.12, U1.P$1
CTRL_2: B1.28, U1.P$2
CTRL_3: B1.27, U2.P$1
CTRL_4: B1.15, U2.P$2
CTRL_5: B1.16, U3.P$1
CTRL_6: B1.26, U3.P$2
D1: B1.29, R13.2, U1.P$26, U2.P$26, U3.P$26
FB2: B1.14, IC1.7, JP2.2, R10.P$2
FB4: B1.17, IC1.1, JP3.2, R11.P$2
FB6: B1.20, IC2.1, JP4.2, R12.P$2
GND: B1.1, B1.4, B1.21, B1.37, B1.40, C4.2, C5.2, C6.2, C7.2, C8.2, C9.2, C10.2, C11.2, C12.2, C13.2, C14.2, C15.2, C16.2, C17.2, C18.2, D2.A, D4.A, D6.A, D8.A, D10.A, D12.A, IC1.4, IC2.4, J2.GND, J2.GNDBREAK, J3.2, JP1.3, R4.1, R5.1, R6.1, R7.2, R8.2, R9.2, R13.1, U1.P$5, U1.P$18, U1.P$19, U1.P$20, U1.P$22, U1.P$23, U1.P$24, U1.P$33, U2.P$5, U2.P$18, U2.P$19, U2.P$20, U2.P$22, U2.P$23, U2.P$24, U2.P$33, U3.P$5, U3.P$18, U3.P$19, U3.P$20, U3.P$22, U3.P$23, U3.P$24, U3.P$33, U4.GND
I_SENSE1: C12.1, IC1.5, R7.1, U1.P$8
I_SENSE2: C13.1, IC1.3, R8.1, U2.P$8
I_SENSE3: C14.1, IC2.3, R9.1, U3.P$8
unnamed: IC1.6, JP2.1, R4.2, R10.P$1
unnamed: IC2.2, JP4.1, R6.2, R12.P$1
unnamed: IC1.2, JP3.1, R5.2, R11.P$1
unnamed: R2.1, U2.P$21
unnamed: C2.2, U2.P$32
unnamed: R3.1, U3.P$21
unnamed: R1.1, U1.P$21
unnamed: C1.2, U1.P$32
unnamed: C3.2, U3.P$32
P_OUT1: D1.A, D2.C, J1.1, U1.P$27, U1.P$28, U1.P$29, U1.P$30
P_OUT2: D3.A, D4.C, J1.2, U1.P$12, U1.P$13, U1.P$14, U1.P$15
P_OUT3: D5.A, D6.C, J1.3, U2.P$27, U2.P$28, U2.P$29, U2.P$30
P_OUT4: D7.A, D8.C, J1.4, U2.P$12, U2.P$13, U2.P$14, U2.P$15
P_OUT5: D9.A, D10.C, J1.5, U3.P$27, U3.P$28, U3.P$29, U3.P$30
P_OUT6: D11.A, D12.C, J1.6, U3.P$12, U3.P$13, U3.P$14, U3.P$15
SLEW: JP1.2, U1.P$3, U2.P$3, U3.P$3
VCC: C1.1, C2.1, C3.1, C4.1, C5.1, C6.1, C7.1, C8.1, C9.1, C15.1, C16.1, C17.1, D1.C, D3.C, D5.C, D7.C, D9.C, D11.C, J2.PWR, J3.3, JP5.1, U1.P$4, U1.P$6, U1.P$11, U1.P$31, U2.P$4, U2.P$6, U2.P$11, U2.P$31, U3.P$4, U3.P$6, U3.P$11, U3.P$31, U4.VIN
